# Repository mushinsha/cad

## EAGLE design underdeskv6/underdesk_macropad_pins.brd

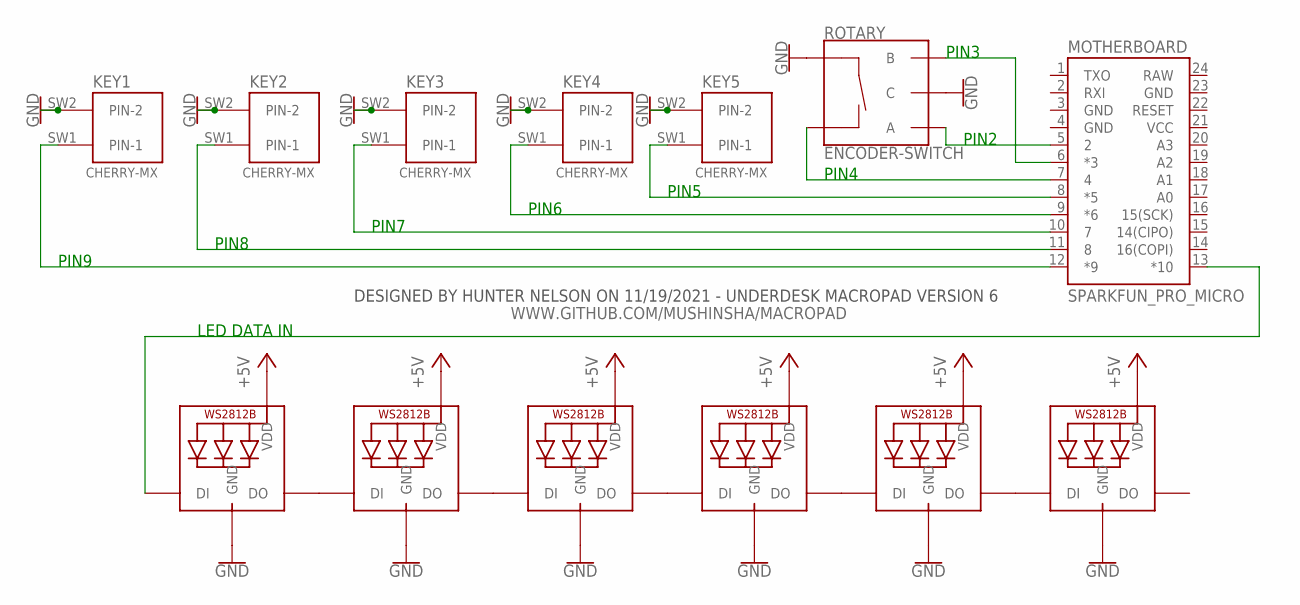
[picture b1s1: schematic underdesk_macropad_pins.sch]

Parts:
KEY1, KEY2, KEY3, KEY4, KEY5: CHERRY-MX
LED1, LED2, LED3, LED4, LED5, LED6: WS2812B5050; WS2812B
MOTHERBOARD: SPARKFUN_PRO_MICRO
ROTARY: ENCODER-SWITCH; ROTARY_ENC_PLAIN

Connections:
+5V: LED1.1-VDD (VDD), LED2.1-VDD (VDD), LED3.1-VDD (VDD), LED4.1-VDD (VDD), LED5.1-VDD (VDD), LED6.1-VDD (VDD)
GND: KEY1.SW2 (PIN-2), KEY2.SW2 (PIN-2), KEY3.SW2 (PIN-2), KEY4.SW2 (PIN-2), KEY5.SW2 (PIN-2), LED1.3-GND (GND), LED2.3-GND (GND), LED3.3-GND (GND), LED4.3-GND (GND), LED5.3-GND (GND), LED6.3-GND (GND), MOTHERBOARD.3 (GND), MOTHERBOARD.4 (GND), MOTHERBOARD.23 (GND), ROTARY.C, ROTARY.SW+
unnamed: LED1.2-DOUT (DO), LED2.4-DIN (DI)
unnamed: LED2.2-DOUT (DO), LED3.4-DIN (DI)
unnamed: LED3.2-DOUT (DO), LED4.4-DIN (DI)
unnamed: LED4.2-DOUT (DO), LED5.4-DIN (DI)
unnamed: MOTHERBOARD.5 (2), ROTARY.A
unnamed: LED1.4-DIN (DI), MOTHERBOARD.13 (*10)
unnamed: MOTHERBOARD.6 (*3), ROTARY.B
unnamed: MOTHERBOARD.7 (4), ROTARY.SW-
unnamed: KEY5.SW1 (PIN-1), MOTHERBOARD.8 (*5)
unnamed: KEY4.SW1 (PIN-1), MOTHERBOARD.9 (*6)
unnamed: KEY3.SW1 (PIN-1), MOTHERBOARD.10 (7)
unnamed: KEY2.SW1 (PIN-1), MOTHERBOARD.11 (8)
unnamed: KEY1.SW1 (PIN-1), MOTHERBOARD.12 (*9)
unnamed: LED5.2-DOUT (DO), LED6.4-DIN (DI)
RAW: MOTHERBOARD.24 (RAW)
VCC: MOTHERBOARD.21 (VCC)

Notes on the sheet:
LED DATA IN
PIN9
PIN8
PIN7
PIN6
PIN5
PIN4
DESIGNED BY HUNTER NELSON ON 11/19/2021 - UNDERDESK MACROPAD VERSION 6
WWW.GITHUB.COM/MUSHINSHA/MACROPAD
PIN3
PIN2

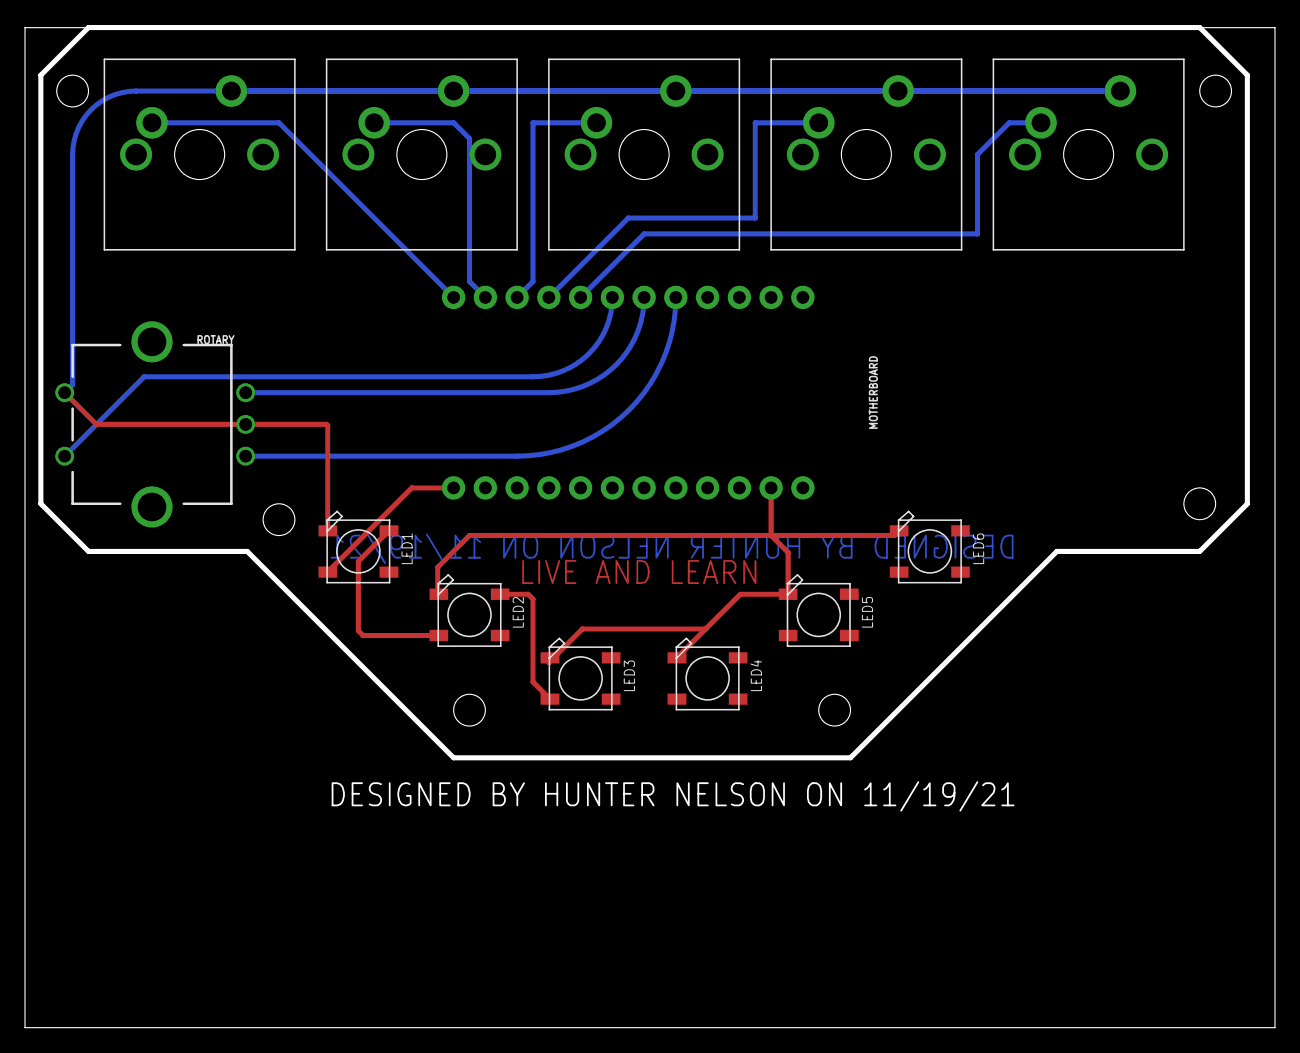
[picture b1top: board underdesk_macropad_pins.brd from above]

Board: 2 copper layers, 100.0 x 80.0 mm, 13 parts (0 on the bottom side), 16 nets.

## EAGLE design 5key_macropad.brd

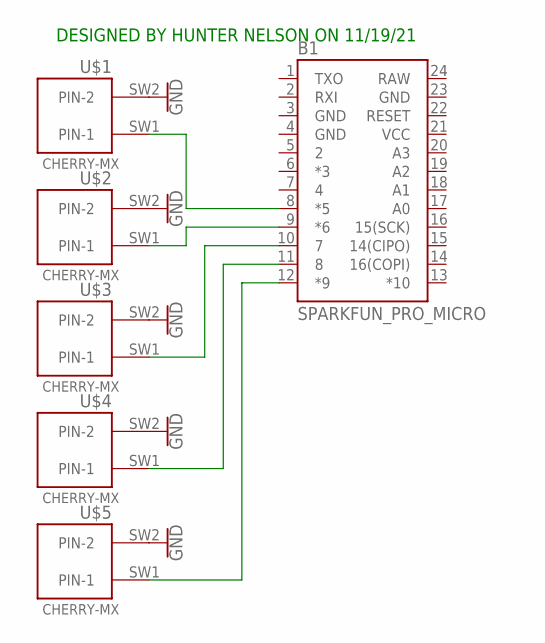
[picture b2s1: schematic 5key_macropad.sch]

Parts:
B1: SPARKFUN_PRO_MICRO
U$1, U$2, U$3, U$4, U$5: CHERRY-MX

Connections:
GND: B1.3 (GND), B1.4 (GND), B1.23 (GND), U$1.SW2 (PIN-2), U$2.SW2 (PIN-2), U$3.SW2 (PIN-2), U$4.SW2 (PIN-2), U$5.SW2 (PIN-2)
unnamed: B1.12 (*9), U$5.SW1 (PIN-1)
unnamed: B1.11 (8), U$4.SW1 (PIN-1)
unnamed: B1.10 (7), U$3.SW1 (PIN-1)
unnamed: B1.9 (*6), U$2.SW1 (PIN-1)
unnamed: B1.8 (*5), U$1.SW1 (PIN-1)
RAW: B1.24 (RAW)
VCC: B1.21 (VCC)

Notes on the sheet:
DESIGNED BY HUNTER NELSON ON 11/19/21

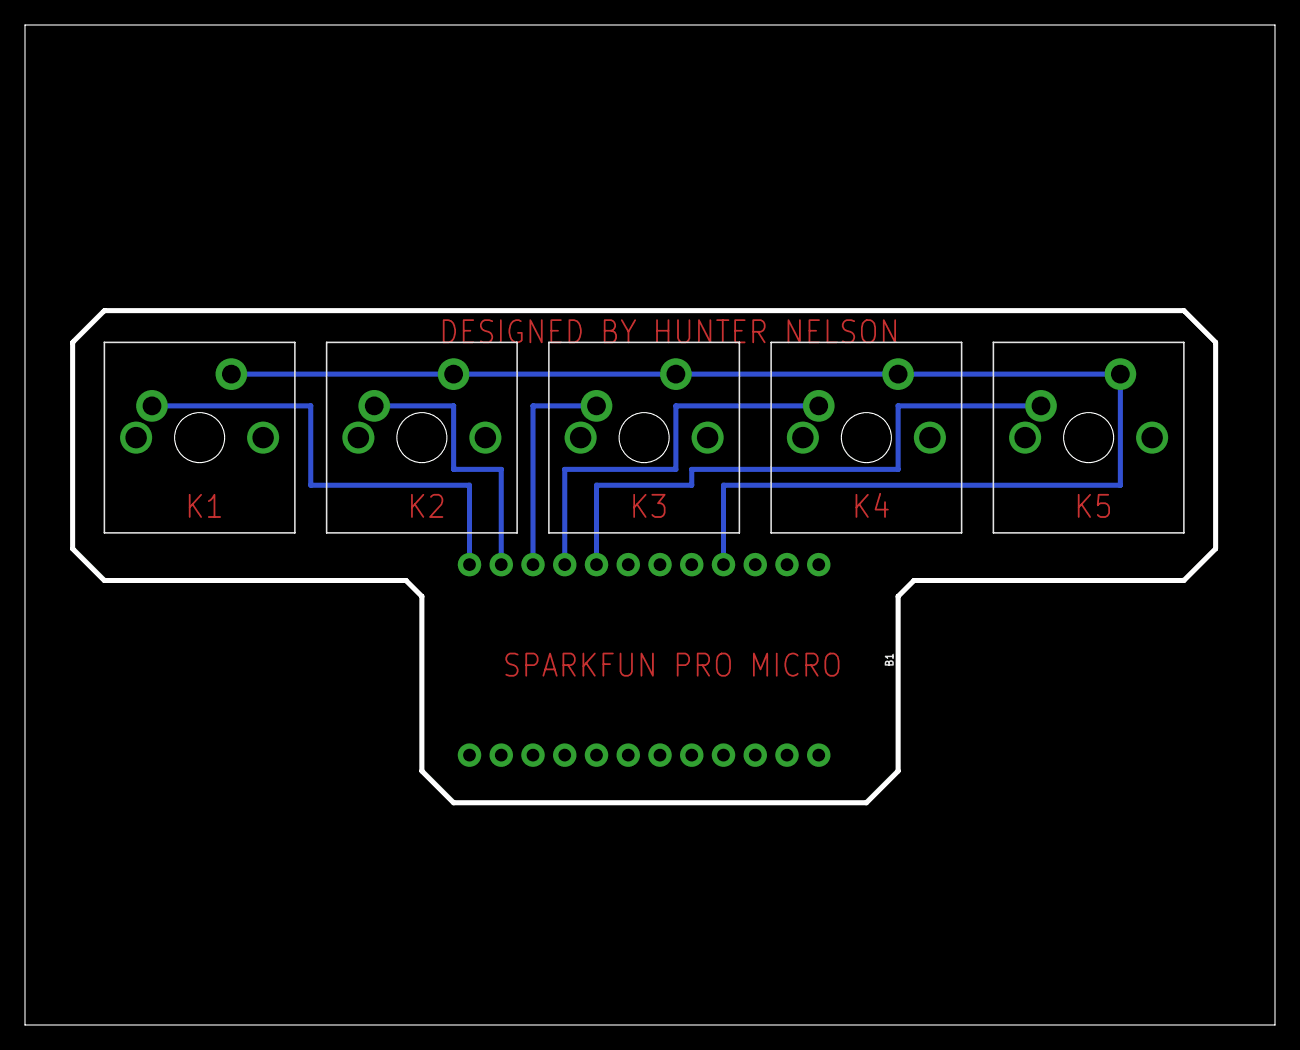
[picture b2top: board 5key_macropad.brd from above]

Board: 2 copper layers, 100.0 x 80.0 mm, 6 parts (0 on the bottom side), 6 nets.

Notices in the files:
parts and their libraries:
SparkFun-Boards: Licensing: Creative Commons ShareAlike 4.0 International - https://creativecommons.org/licenses/by-sa/4.0
